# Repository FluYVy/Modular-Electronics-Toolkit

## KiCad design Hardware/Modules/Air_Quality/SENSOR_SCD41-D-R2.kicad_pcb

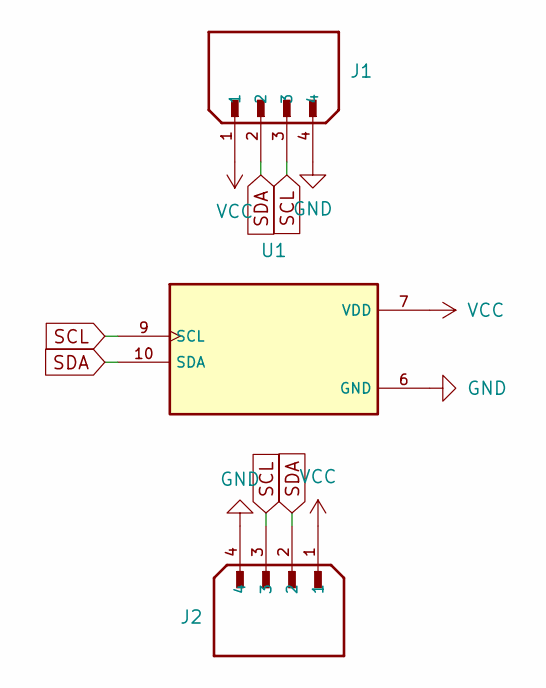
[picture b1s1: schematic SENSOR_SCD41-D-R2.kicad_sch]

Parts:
J1, J2: JST_EH_B4B-EH-A_1x04_P2.50mm_Vertical
U1: Sensirion_SCD4x-1EP_10.1x10.1mm_P1.25mm_EP4.8x4.8mm

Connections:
GND: J1.4, J2.4, U1.6 (GND), U1.20 (GND__1), U1.21 (GND__2)
SCL: J1.3, J2.3, U1.9 (SCL)
SDA: J1.2, J2.2, U1.10 (SDA)
VCC: J1.1, J2.1, U1.7 (VDD), U1.19 (VDDH)

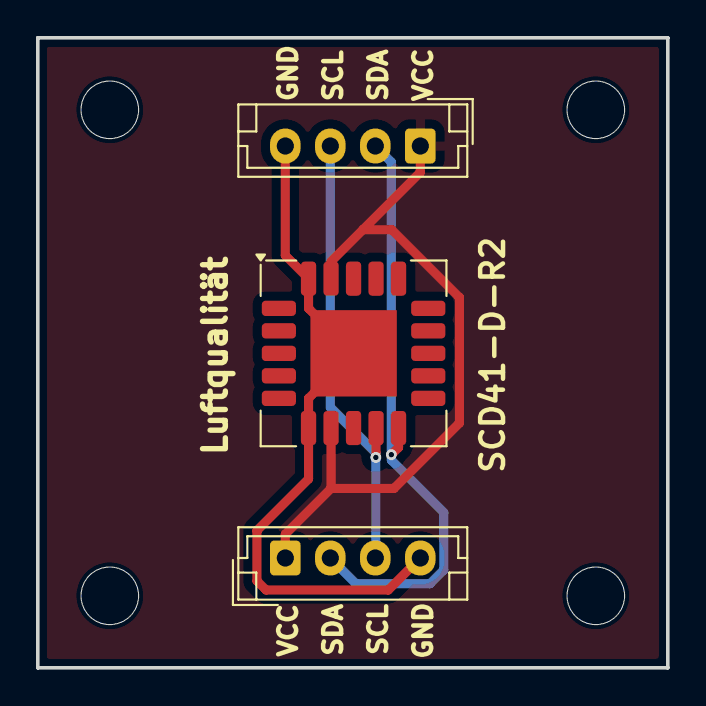
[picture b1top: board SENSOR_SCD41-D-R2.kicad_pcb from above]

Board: 2 copper layers, 35.0 x 35.0 mm, 3 parts (0 on the bottom side), 4 nets.

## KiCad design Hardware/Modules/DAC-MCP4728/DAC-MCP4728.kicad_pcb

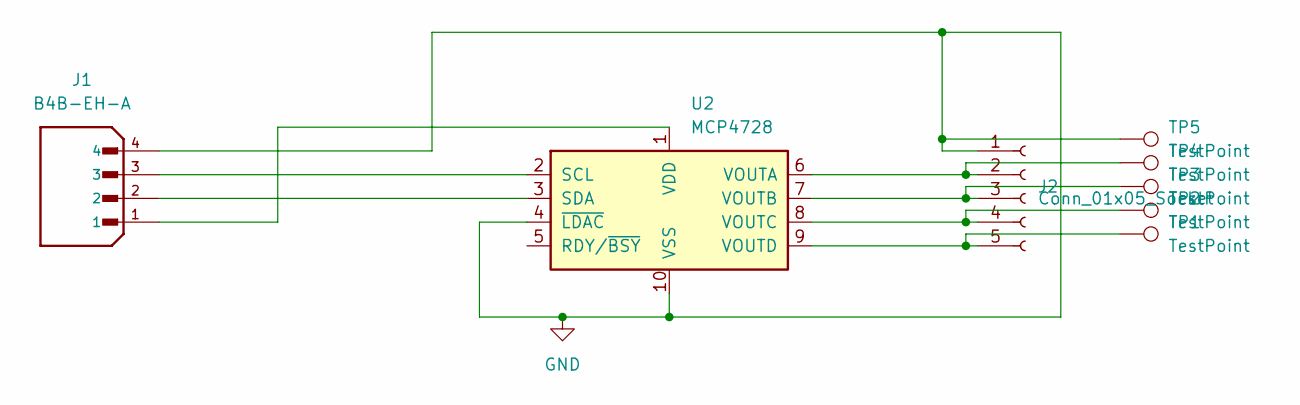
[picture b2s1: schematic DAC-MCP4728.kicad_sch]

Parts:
J1: B4B-EH-A; JST_EH_B4B-EH-A_1x04_P2.50mm_Vertical
J2: Conn_01x05_Socket; PinSocket_1x05_P2.54mm_Vertical
TP1, TP2, TP3, TP4, TP5: TestPoint; TestPoint_Pad_1.0x1.0mm
U2: MCP4728; TSSOP-10_3x3mm_P0.5mm

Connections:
GND: J1.4, J2.1, TP5.1, U2.4 (~LDAC), U2.10 (VSS)
unnamed: J2.2, TP4.1, U2.6 (VOUTA)
unnamed: J2.3, TP3.1, U2.7 (VOUTB)
unnamed: J2.4, TP2.1, U2.8 (VOUTC)
unnamed: J2.5, TP1.1, U2.9 (VOUTD)
unnamed: J1.3, U2.2 (SCL)
unnamed: J1.2, U2.3 (SDA)
unnamed: J1.1, U2.1 (VDD)

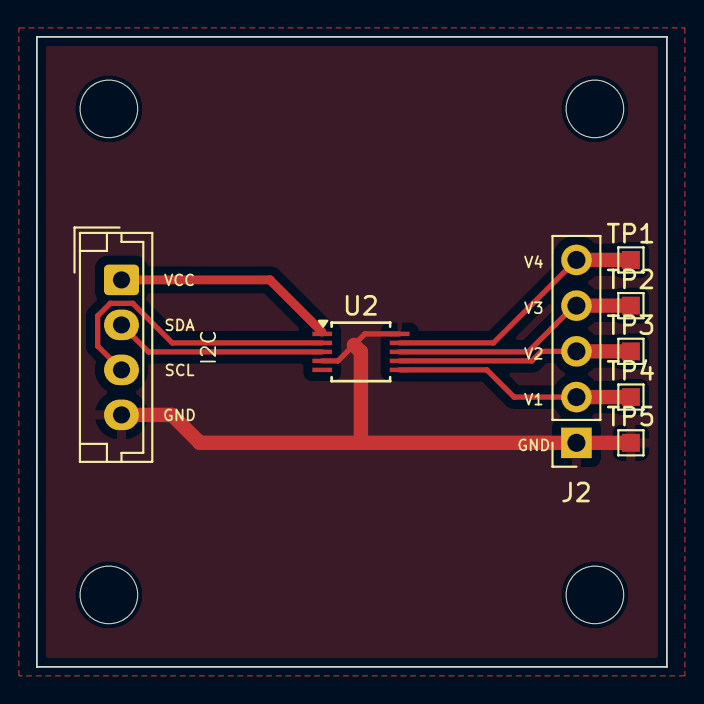
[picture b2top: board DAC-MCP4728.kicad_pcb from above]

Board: 2 copper layers, 35.0 x 35.0 mm, 8 parts (0 on the bottom side), 8 nets.
